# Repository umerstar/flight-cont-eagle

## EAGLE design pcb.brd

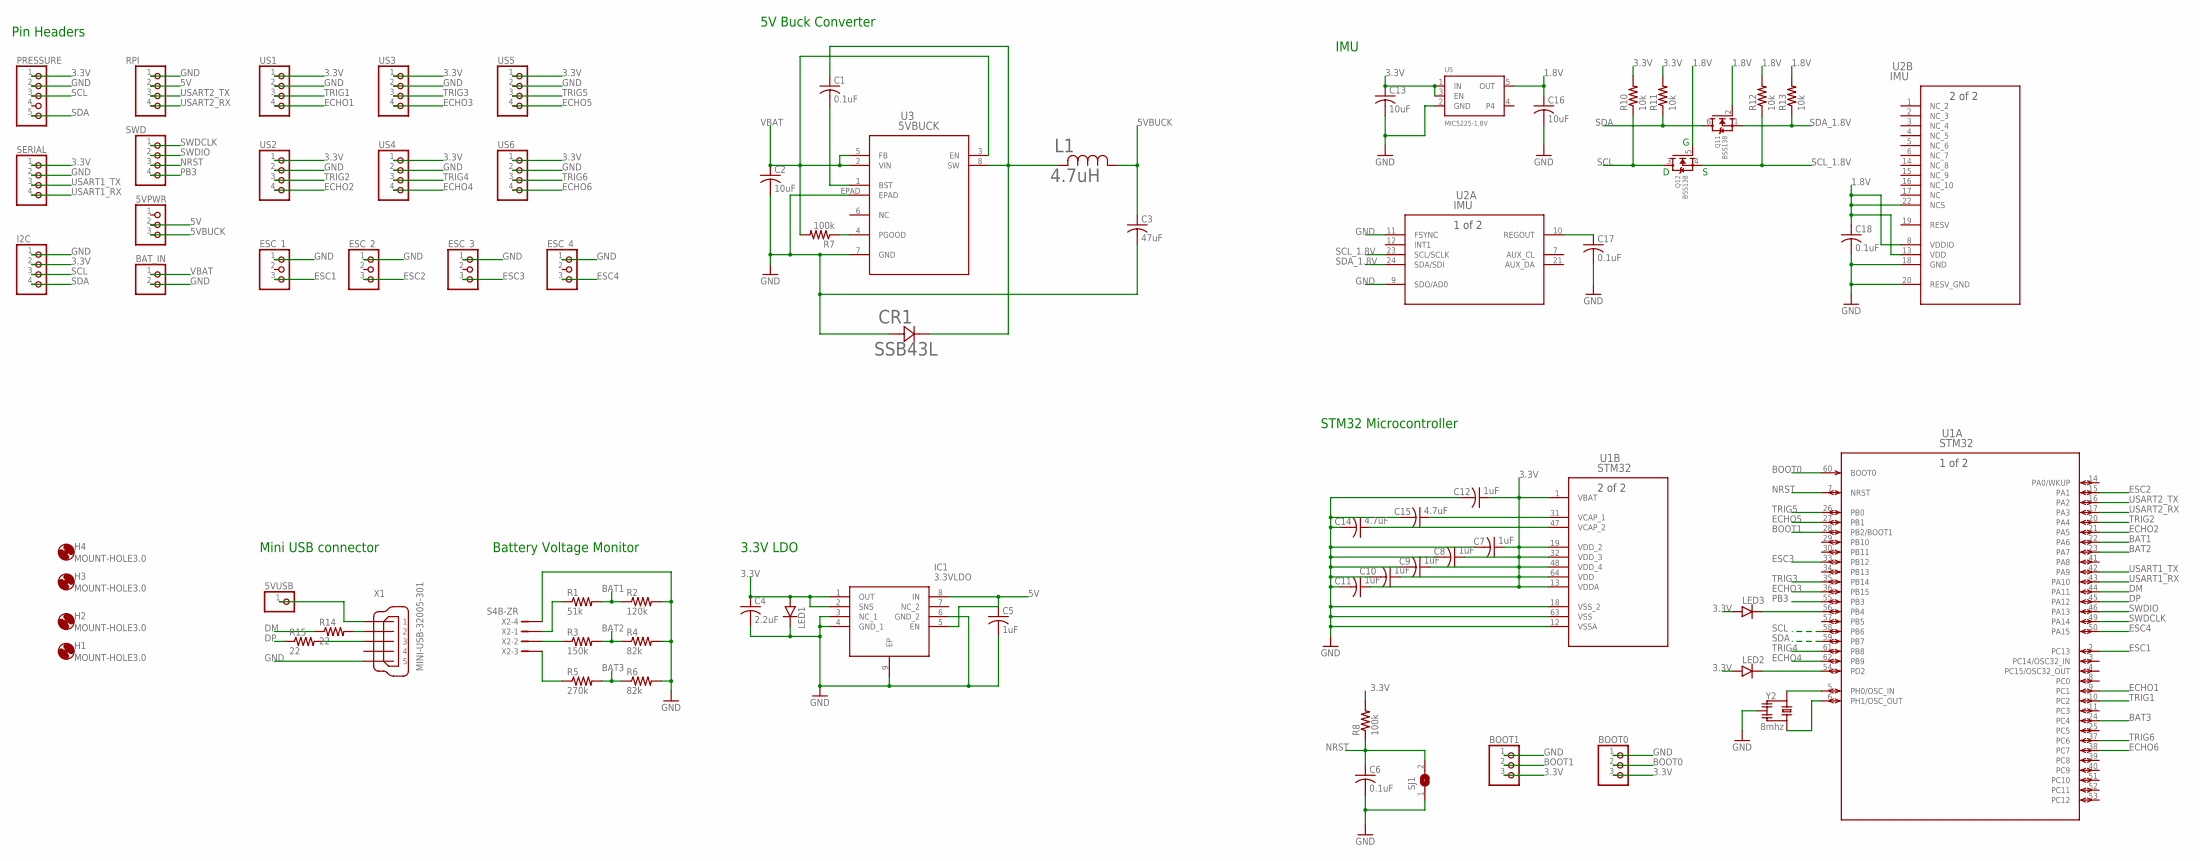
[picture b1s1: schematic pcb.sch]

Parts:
5VPWR: PINHD-1X3; 1X03
5VUSB: PINHD-1X1; 1X01
BAT_IN: PINHD-1X2; 1X02
BOOT0, BOOT1: PINHD-1X3; 1X03
C1, C6, C17, C18: 0.1uF; C0805
C2, C13, C16: 10uF; C0805
C3: 47uF; C0805
C4: 2.2uF; C0805
C5, C7, C8, C9, C10, C11, C12: 1uF; C0805
C14, C15: 4.7uF; C0805
CR1: SSB43L; DIODE_DO214AA_MBRS-M
ESC_1, ESC_2, ESC_3, ESC_4: PINHD-1X3; 1X03
H1, H2, H3, H4: MOUNT-HOLE3.0; 3,0
I2C: PINHD-1X4; 1X04
IC1: 3.3VLDO; SOP65P490X110-9N
L1: 4.7uH; IND_B82464G4_EPC
LED1, LED2, LED3: SMD-CHIP-LED-0805
PRESSURE: PINHD-1X5; 1X05
Q1: BSS138; SOT363
R1: 51k; R0805
R2: 120k; R0805
R3: 150k; R0805
R4, R6: 82k; R0805
R5: 270k; R0805
R7, R8: 100k; R0805
R10, R11, R12, R13: 10k; R0805
R14, R15: 22; R0805
RPI: PINHD-1X4; 1X04
SERIAL: PINHD-1X4; 1X04
SJ1: SJ
SWD: PINHD-1X4; 1X04
U1: STM32; LQFP64-10X10MM
U2: IMU; QFN24_3X3X0P9_IVS
U3: 5VBUCK; RD_8_1_ADI-M
U5: MIC5225-1.8V; SOT23-5
US1, US2, US3, US4, US5, US6: PINHD-1X4; 1X04
X1: MINI-USB-32005-301; 32005-301
X2: S4B-ZR
Y2: 8mhz; RESONATOR_8

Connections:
1.8V: C16.1, C18.1, Q1.2 (G), Q1.5 (G), R12.2, R13.2, U2.8 (VDDIO), U2.13 (VDD), U2.22 (NCS), U5.5 (OUT)
3.3V: BOOT0.3, BOOT1.3, C4.1, C7.1, C8.1, C9.1, C10.1, C11.1, C12.1, C13.1, I2C.2, IC1.1 (OUT), IC1.2 (SNS), LED1.A, LED2.A, LED3.A, PRESSURE.1, R8.2, R10.2, R11.2, SERIAL.1, U1.1 (VBAT), U1.13 (VDDA), U1.19 (VDD_2), U1.32 (VDD_3), U1.48 (VDD_4), U1.64 (VDD), U5.1 (IN), U5.3 (EN), US1.1, US2.1, US3.1, US4.1, US5.1, US6.1
5V: 5VPWR.2, C5.1, IC1.5 (EN), IC1.8 (IN), RPI.2
5VBUCK: 5VPWR.3, C3.1, L1.1
BAT1: R1.2, R2.1, U1.22 (PA6)
BAT2: R3.2, R4.1, U1.23 (PA7)
BAT3: R5.2, R6.1, U1.24 (PC4)
BOOT0: BOOT0.2, U1.60 (BOOT0)
BOOT1: BOOT1.2, U1.28 (PB2/BOOT1)
DM: R14.1, U1.44 (PA11)
DP: R15.1, U1.45 (PA12)
ECHO1: U1.9 (PC1), US1.4
ECHO2: U1.21 (PA5), US2.4
ECHO3: U1.36 (PB15), US3.4
ECHO4: U1.62 (PB9), US4.4
ECHO5: U1.27 (PB1), US5.4
ECHO6: U1.38 (PC7), US6.4
ESC1: ESC_1.3, U1.2 (PC13)
ESC2: ESC_2.3, U1.15 (PA1)
ESC3: ESC_3.3, U1.33 (PB12)
ESC4: ESC_4.3, U1.50 (PA15)
GND: BAT_IN.2, BOOT0.1, BOOT1.1, C2.2, C3.2, C4.2, C5.2, C6.2, C7.2, C8.2, C9.2, C10.2, C11.2, C12.2, C13.2, C14.2, C15.2, C16.2, C17.2, C18.2, CR1.2, ESC_1.1, ESC_2.1, ESC_3.1, ESC_4.1, I2C.1, IC1.3 (NC_1), IC1.4 (GND_1), IC1.6 (GND_2), IC1.9 (EP), LED1.C, PRESSURE.2, R2.2, R4.2, R6.2, RPI.1, SERIAL.2, SJ1.1, U1.12 (VSSA), U1.18 (VSS_2), U1.63 (VSS), U2.9 (SDO/AD0), U2.11 (FSYNC), U2.18 (GND), U2.20 (RESV_GND), U3.7 (GND), U3.EPAD, U5.2 (GND), US1.2, US2.2, US3.2, US4.2, US5.2, US6.2, X1.5, X2.4, Y2.2
unnamed: R5.1, X2.3
unnamed: C17.1, U2.10 (REGOUT)
unnamed: R14.2, X1.2
unnamed: R3.1, X2.2
unnamed: R1.1, X2.1
unnamed: U1.5 (PH0/OSC_IN), Y2.1
unnamed: R15.2, X1.3
unnamed: 5VUSB.1, X1.1
unnamed: U1.6 (PH1/OSC_OUT), Y2.3
unnamed: C1.2, U3.1 (BST)
unnamed: R7.1, U3.4 (PGOOD)
unnamed: C1.1, CR1.1, L1.2, U3.8 (SW)
unnamed: C15.1, U1.31 (VCAP_1)
unnamed: C14.1, U1.47 (VCAP_2)
unnamed: LED3.C, U1.56 (PB4)
unnamed: LED2.C, U1.54 (PD2)
NRST: C6.1, R8.1, SJ1.2, SWD.3, U1.7 (NRST)
PB3: SWD.4, U1.55 (PB3)
SCL: I2C.3, PRESSURE.3, Q1.3 (D), R10.1, U1.58 (PB6)
SCL_1.8V: Q1.4 (S), R12.1, U2.23 (SCL/SCLK)
SDA: I2C.4, PRESSURE.5, Q1.6 (D), R11.1, U1.59 (PB7)
SDA_1.8V: Q1.1 (S), R13.1, U2.24 (SDA/SDI)
SWDCLK: SWD.1, U1.49 (PA14)
SWDIO: SWD.2, U1.46 (PA13)
TRIG1: U1.10 (PC2), US1.3
TRIG2: U1.20 (PA4), US2.3
TRIG3: U1.35 (PB14), US3.3
TRIG4: U1.61 (PB8), US4.3
TRIG5: U1.26 (PB0), US5.3
TRIG6: U1.37 (PC6), US6.3
USART1_RX: SERIAL.4, U1.43 (PA10)
USART1_TX: SERIAL.3, U1.42 (PA9)
USART2_RX: RPI.4, U1.17 (PA3)
USART2_TX: RPI.3, U1.16 (PA2)
VBAT: BAT_IN.1, C2.1, R7.2, U3.2 (VIN), U3.3 (EN), U3.5 (FB)

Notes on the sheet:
IMU
5V Buck Converter
3.3V LDO
Pin Headers
STM32 Microcontroller
Battery Voltage Monitor
Mini USB connector

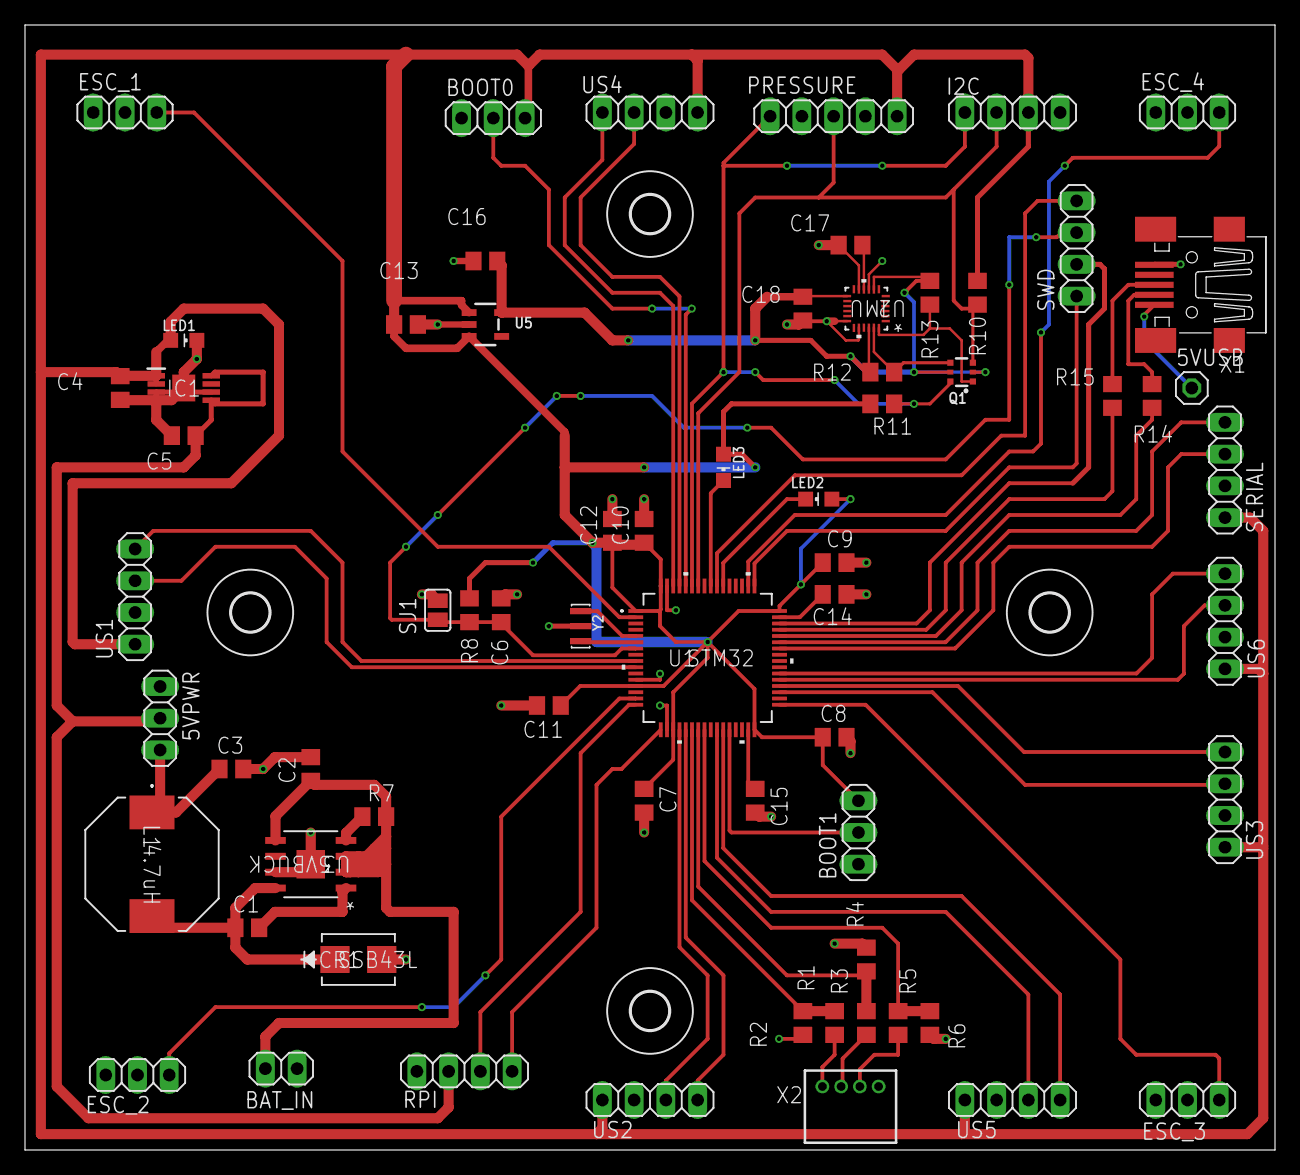
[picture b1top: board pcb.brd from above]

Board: 2 copper layers, 100.0 x 90.0 mm, 71 parts (0 on the bottom side), 57 nets.

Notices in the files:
parts and their libraries:
COPYRIGHT: Copyright (C) 2018 Accelerated Designs. All rights reserved
alienflight: License: CC BY SA
